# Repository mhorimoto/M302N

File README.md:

# M302N3

New hardware that improves on the M302K to make it smaller, more dedicated and no-code.

M302Kを改良して小型化、専用化とノーコード化を目指した新しいハードウェア  
M302N2を使用して、
* 気温湿度
* CO2
* 光量子 or 日射量
* 土中水分

を1台で観測可能とする

ここまでが M302N2-ULTRA これからが、M302N3 本当のPoEを採用する

## Main specifications

## パーツリスト

N3のための新規パーツ（現在検討中）

+ RJ-45モジュール Pulse YAGEO J00-0065NL
+ PoE モジュール Silvertel Ag9912-MT 12V出力の工業規格

## 主諸元
+ I2CとADC入力を備えたUECS測定ノード機
+ I/Oは5V
+ 電源電圧はDC12V/1A(Max)
+ M800系のPoEは使えなくなる

## Revision List

### 1.00 初版 (2025/03/09)
### 2.00 
* J1の結線ミスを修正 (Done 2025/05/12)
* J2のUARTはSoftwareSerial対応にして、D0,D1を空けておき、D8,D9をRX,TXに割り当てる。5V Vccの追加。 (Done 2025/05/12)
* J3の対応ピンを変更する。Hardware InterruptのD2,D3を入力端子として扱えるように。D2,3,4,5,6,7 (Done 2025/05/12)
* LED-D2はA0に割り当てる
* J9,J10 の削除 (Done 2025/05/12)
* J11 止め穴を0.1mm大きくする
* SW1はXH-B2Bに変更 (Done 2025/05/12)
* J1へCPUから5Vが逆流しないように1S4を追加 (Done 2025/05/12)
### 3.00

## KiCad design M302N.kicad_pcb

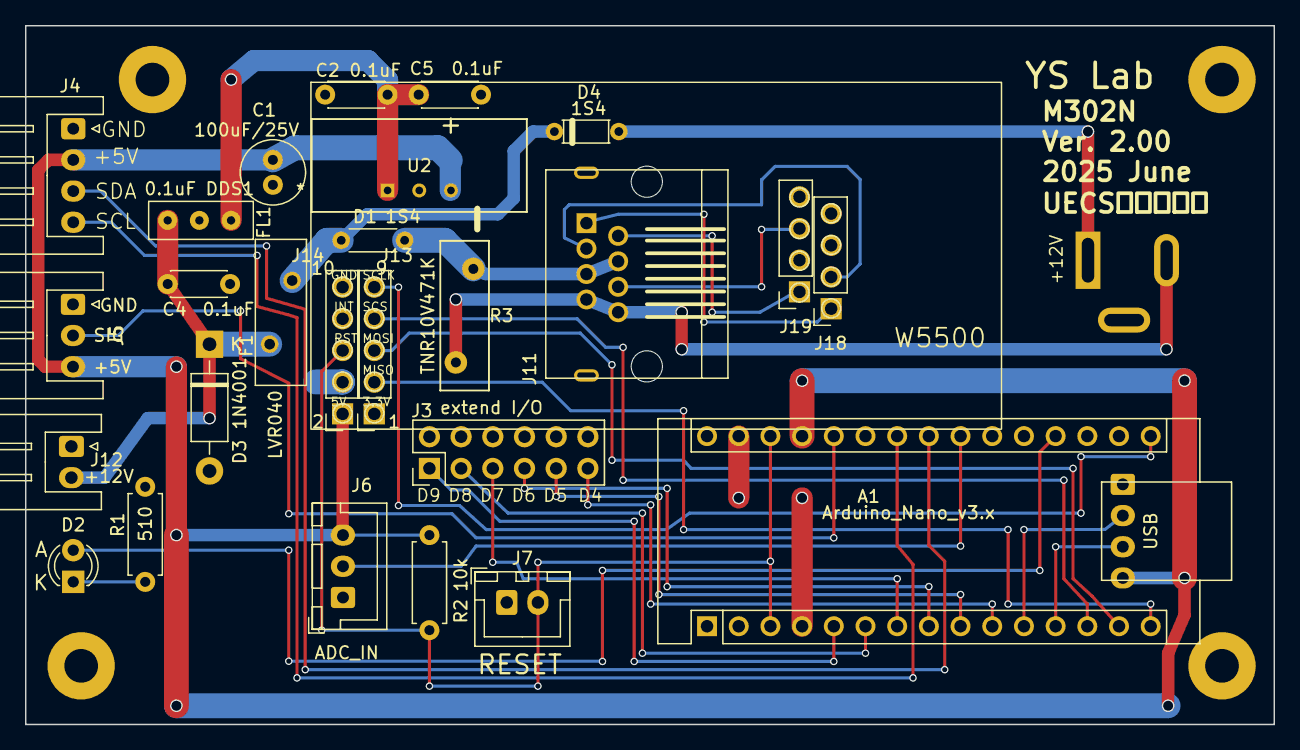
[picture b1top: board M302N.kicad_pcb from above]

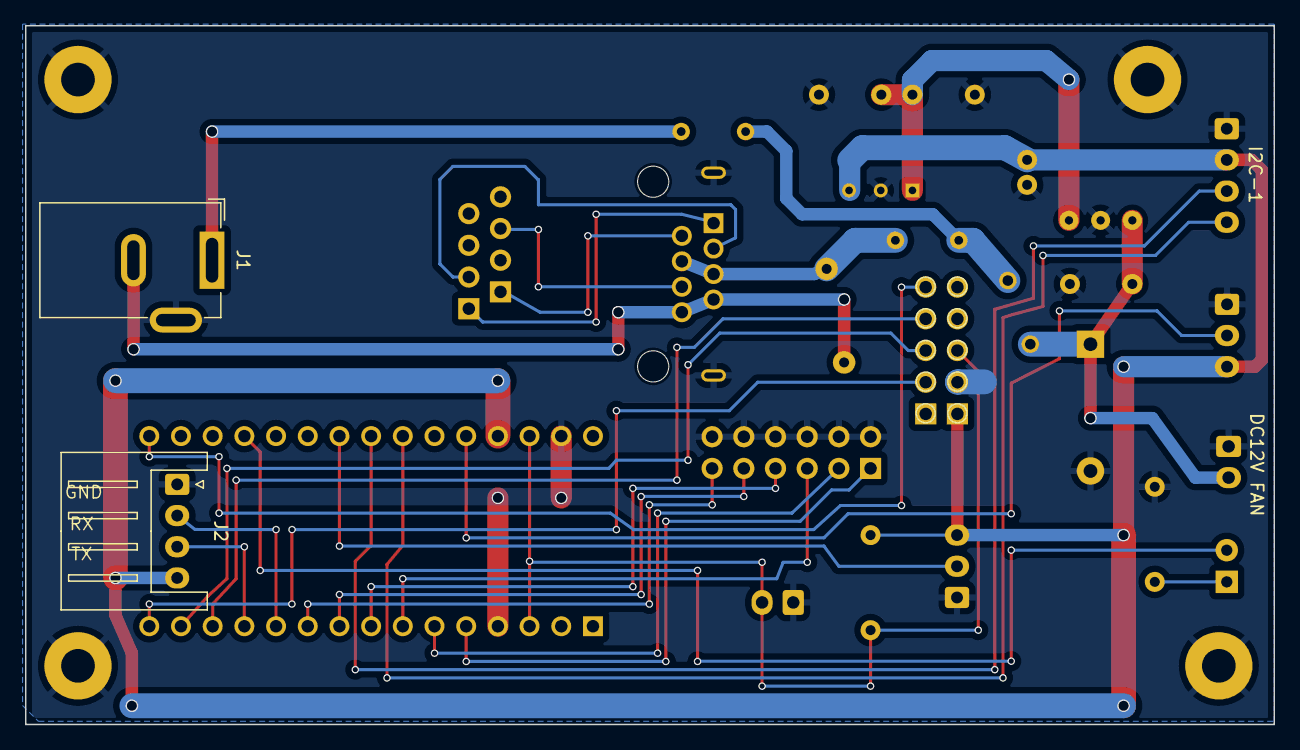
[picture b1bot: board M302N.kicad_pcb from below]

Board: 2 copper layers, 100.1 x 56.0 mm, 29 parts (2 on the bottom side), 31 nets.

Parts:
A1: Arduino_Nano_v3.x; Arduino_Nano
C1: 100uF/25V; C_Radial_D5.0mm_H11.0mm_P2.00mm
C2, C4, C5: 0.1uF; C_Disc_D4.3mm_W1.9mm_P5.00mm
D1, D4: 1S4; R_Axial_DIN0204_L3.6mm_D1.6mm_P5.08mm_Horizontal
D2: LED; LED_D3.0mm
D3: 1N4001; D_DO-41_SOD81_P10.16mm_Horizontal
F1: LVR040; Fuse_BelFuse_0ZRE0033FF_L11.4mm_W3.8mm
FL1: 0.1uF DDS1; DSS1
J1: DC12V; BarrelJack_GCT_DCJ200-10-A_Horizontal
J2: UART; JST_XH_S4B-XH-A_1x04_P2.50mm_Horizontal
J3: extend I/O; PinHeader_2x06_P2.54mm_Vertical
J4: I2C-1; JST_XH_S4B-XH-A_1x04_P2.50mm_Horizontal
J5: ADC_IN; JST_XH_S3B-XH-A_1x03_P2.50mm_Horizontal
J6: ADC_IN; JST_XH_B3B-XH-A_1x03_P2.50mm_Vertical
J7: RESET; JST_XH_B2B-XH-A_1x02_P2.50mm_Vertical
J11: RJ45; RJ45_Neltron_7810-8P8C
J12: DC12V FAN; JST_XH_S2B-XH-A_1x02_P2.50mm_Horizontal
J13, J14: Conn_01x05_Socket; PinSocket_1x05_P2.54mm_Vertical
J18, J19: Conn_01x04_Socket; PinSocket_1x04_P2.54mm_Vertical
R1: 510; R_Axial_DIN0207_L6.3mm_D2.5mm_P7.62mm_Horizontal
R2: 10k; R_Axial_DIN0207_L6.3mm_D2.5mm_P7.62mm_Horizontal
R3: TNR10V471K; RV_Disc_D12mm_W3.9mm_P7.5mm
U1: W5500; W5500LARGE
U2: BP5293-50; SIP03_BP5293_17X7P2_ROM

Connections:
+5V: A1.27 (+5V), C1.1, J2.4, J4.2, J5.3, J6.3, J14.1, R2.1, U2.3 (VOUT)
/*D10/SS: A1.13 (D10), J13.4
/*D11/MOSI: A1.14 (D11), J13.3
/+12V: D1.1 (K), D4.1 (K), F1.2
/A4/SDA: A1.23 (A4), J4.3
/A5/SCL: A1.24 (A5), J4.4
/D12/MISO: A1.15 (D12), J13.2
/RX: A1.11 (D8), J2.2
/TX: A1.12 (D9), J2.3
/~RESET: A1.3 (~RESET), A1.28 (~RESET), J7.2, J14.3, R2.2
GND: A1.4 (GND), A1.29 (GND), C1.2, C2.2, C4.2, C5.2, D3.2 (A), FL1.2, J1.3, J2.1, J3.2, J3.4, J3.6, J3.8, J3.10, J3.12, J4.1, J5.1, J6.1, J7.1, J12.1, J14.2, R1.2, U2.2 (GND)
unnamed: A1.19 (A0), D2.2 (A)
unnamed: A1.22 (A3), J6.2
unnamed: A1.26 (A7), J5.2
unnamed: A1.5 (D2), J3.1
unnamed: A1.6 (D3), J3.3
unnamed: A1.7 (D4), J3.5
unnamed: A1.8 (D5), J3.7
unnamed: A1.9 (D6), J3.9
unnamed: A1.10 (D7), J3.11
unnamed: A1.16 (D13), J13.5
unnamed: D1.2 (A), J11.4, J11.5, R3.2
unnamed: D2.1 (K), R1.1
unnamed: C4.1, D3.1 (K), F1.1, FL1.3, J12.2
unnamed: D4.2 (A), J1.1
unnamed: J1.2, J11.7, J11.8, R3.1
unnamed: J11.1, J18.1
unnamed: J11.3, J18.2
unnamed: J11.2, J19.1
unnamed: J11.6, J19.3
unnamed: C2.1, C5.1, FL1.1, U2.1 (VIN)

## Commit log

2025-02-18 3D data fan fannel
2025-02-25 W5500新しいシンボルとフットパターン
2025-02-26 W5500との接続はソケット
2025-02-28 PCB設計途中
2025-03-03 PCB設計とRJ45モジュラー
2025-03-04 PCB設計中
2025-03-04 PCB継続
2025-03-05 PCB基本完成・文字入れなど未完
2025-03-05 PCBほぼ完成
2025-03-06 3D機構データ
2025-03-07 3Dデータ更新とRJ45コネクタの取り付け位置微妙に変更
2025-03-07 もうすぐ完成
2025-03-09 PCB発注
2025-03-11 機構部品を設計
2025-03-12 機構部品製作
2025-03-13 機構部品ほぼ合わせ終わり
2025-03-17 底板のデザイン変更
2025-04-02 NC-PoEアクリル基板図面
2025-04-02 V2.00はじめ
2025-05-12 回路図上の変更は完了。PCB部品の選定に入る所。
2025-05-13 READMEに注意書きを行う
2025-05-14 PoE 802.3afの検討の続き
2025-06-02 v2.00 PCB変更とスイッチングレギュレータ採用検討
2025-06-03 DCDC converter
2025-06-03 大胆な変更
2025-06-03 v2.00 ほぼ完成？
2025-06-04 PCBのdesign rule check中
2025-06-27 Ver2.00
2025-06-27 v2.00 BOM schema print
2025-07-14 更新し直し
2025-08-29 gitignore
2025-08-29 KiCAD 9.0
2025-09-21 センサー類をシンボル化
2025-09-27 Soilを編集中
2025-09-28 ULTRA初版・まだタイトルなし
2025-09-29 外観デザインスケッチを追加
2025-09-30 アイディアスケッチ追加
2025-10-01 ULTRA ver 1.00
2025-10-01 ULTRA ver 2.00
2025-10-01 Ver 2.10 Append DDS
2025-10-03 パイプ実装のための3Dプリント素材追加
2026-04-25 PoE部品の選定など
